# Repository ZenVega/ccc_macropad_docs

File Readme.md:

# CCC macropad

## Installation

### QMK Cli
This is just a quick recap. When you get stuck, check the official qmk documentation [here](https://docs.qmk.fm/newbs_getting_started)
In order to get QMK installed on your system run
'python3 -m pip install qmk'
Test if installation was successfull:
'qmk --version'

If you want to start from scratch follow the upcoming instructions. In case you just want to flash your macropad jump [here](#flash_build).

### QMK Setup

'qmk setup'
this will install the qmk firmware
submit prompts with 'y'

You should now have QMK setup in '~/qmk_firmware'.

### Create new layout
```bash
cd ~/qmk_firmware/keyboards
qmk new-keyboard
```

follow the instructions. when it comes to the board, choose: 

->non of the above layouts

->15. promicro_rp2040

your new keyboard's setup should now be created in: 

```bash
~/qmk_firmware/keyboards/<your_keyboards_name_folder>
```

in you keyboard.json:
add: 
```yaml
"via": true
``` 
to the features

add: 
```yaml
  "analog": {
    "pins": ["GP26"]
  },
```
This adds the potential use of variable resistors connected to pin26.

The 'keyboard.yaml' holds the actual layout of the keyboard as well as some more metadata.
You may have multiple keymaps holding different configurations for this layout.
After configuring your keymap to your liking, you can always try to compile and see if you keymap.c and you kayboard.yaml align:

### Flash macropad {# flash_build}
However if you want to work with the layout we provide clone this [repo] (https://github.com/ZenVega/qmk_for_macropad/tree/main) containing the firmware and the macropad layout and keymap.
Or you use the cloned firmware and copy/past the all keyboard config files in the equivalent folder.
To install all missing dependencies run:

```bash
git submodule update --init --recursive

git submodule sync --recursive
git submodule update --init --recursive --force
```

### Compiling
This will create a *.bin that holds the firmware including your compilation ready to be flashed on the MCU

```bash
qmk compile -kb <keyboard> -km <keymap>
```
you should find a '<your_keyboard>

if not defined differently you keymap is just 'default'

### Flashing your MCU
Once you are ready to flash qmk to your microcontroller (rp2040 in this case), plug it in and set it into bootloader mode.
In our case that requires pressing the boot button while plugging it in. The device should show up as a flashable media in your files-explorer.
run:

```bash
qmk flash -kb <keyboard> -km <keymap>
```

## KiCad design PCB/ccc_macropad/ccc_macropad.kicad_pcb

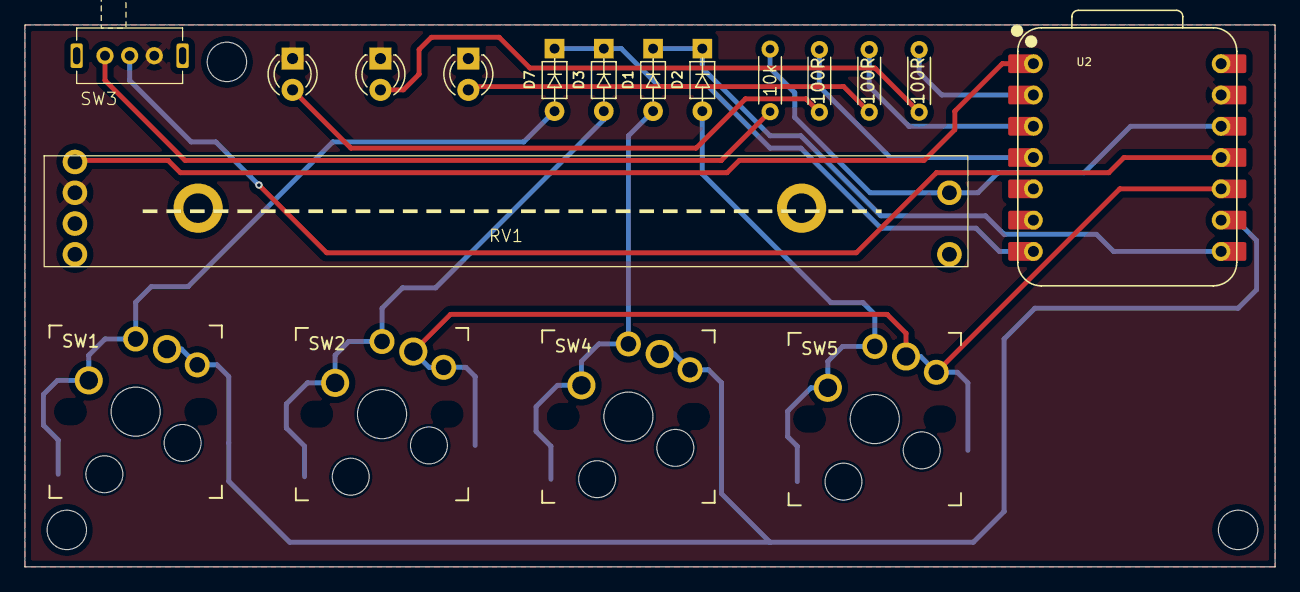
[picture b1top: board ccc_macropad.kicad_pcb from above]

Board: 2 copper layers, 101.5 x 44.0 mm, 18 parts (0 on the bottom side), 19 nets.

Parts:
10k: 10k; R_Axial_DIN0204_L3.6mm_D1.6mm_P5.08mm_Horizontal
100R, 100R#2, 100R#3: 100R; R_Axial_DIN0204_L3.6mm_D1.6mm_P5.08mm_Horizontal
D1, D2, D3, D7: 1N4148WT; D_DO-35_SOD27_P5.08mm_Horizontal
D6 LED, D8 LED, D9 LED: LED; LED_D3.0mm
RV1: Analogue_input_slider 10k; Potentiometer_slide_75mm_range_60mm_2_sets
SW1, SW2, SW4, SW5: SW_Push; Kailh_socket_MX_PG1350_optional
SW3: OS/Left_Right-hand_Switch; SPDT_3pin_2_pos_1P2T_tht_2.54mm_switch_sk12d07
U2: XIAO-RP2040-DIP

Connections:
GND: D6 LED.1 (K), D8 LED.1 (K), D9 LED.1 (K), RV1.1, SW3.3 (A), U2.13 (GND)
unnamed: D1.2 (A), SW4.2
unnamed: D1.1 (K), D2.1 (K), U2.8 (GPIO1/RX)
unnamed: D2.2 (A), SW5.2
unnamed: D3.2 (A), SW2.2
unnamed: D3.1 (K), D7.1 (K), U2.7 (GPIO0/TX)
unnamed: 100R#3.1, D6 LED.2 (A)
unnamed: D7.2 (A), SW1.2
unnamed: 100R.1, D8 LED.2 (A)
unnamed: 100R#2.1, D9 LED.2 (A)
unnamed: SW3.2 (B), U2.11 (GPIO3/MOSI)
unnamed: 10k.1, SW3.1 (C)
unnamed: 10k.2, RV1.3, U2.12 (3V3)
unnamed: SW1.1, SW4.1, U2.9 (GPIO2/SCK)
unnamed: SW2.1, SW5.1, U2.10 (GPIO4/MISO)
unnamed: RV1.2, U2.1 (GPIO26/ADC0/A0)
unnamed: 100R#2.2, U2.2 (GPIO27/ADC1/A1)
unnamed: 100R.2, U2.3 (GPIO28/ADC2/A2)
unnamed: 100R#3.2, U2.4 (GPIO29/ADC3/A3)

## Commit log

2025-09-23 chores: add installation guide to readme
2025-09-23 chores: qmk config to readme
2025-09-24 chores: add readme flashing rp2040
2025-09-24 chores: add readme flash mcu
2025-09-24 chores: codeblock formatting
2025-09-24 chores: add variable resistor to yaml
2025-09-24 chores: update installation guide and remote qmk URL
2025-09-24 fix: target branch
2025-09-24 kicad:feat: add schematics
2025-09-24 kicad:chores: remove backups from repo
2025-10-02 macropad:feature: add LED's and footprints
2025-10-02 feat: create BOM including order links
2025-10-02 feat: update BOM and OS_switch
2025-10-04 feat: create and include all footprint. import all components in PCB
2025-10-06 pcb:routing
2025-10-10 PCB:feat: update footprint slider
2025-10-10 PCB:feat: update footprint spdt switch
2025-10-10 chores: font / fontsize
2025-10-12 PCB:feat: add ground plane / add mounting holes / route thickness .4mm
2025-10-16 fix: footprint switch / add ground plane front
2025-10-16 chores: rm gerber zip
2025-10-16 rm font / add front ground plane
2025-10-17 art for prototype added to KiCad
2025-10-17 chores: add to .gitignore
2025-10-17 extra: private notes and .gitignore
